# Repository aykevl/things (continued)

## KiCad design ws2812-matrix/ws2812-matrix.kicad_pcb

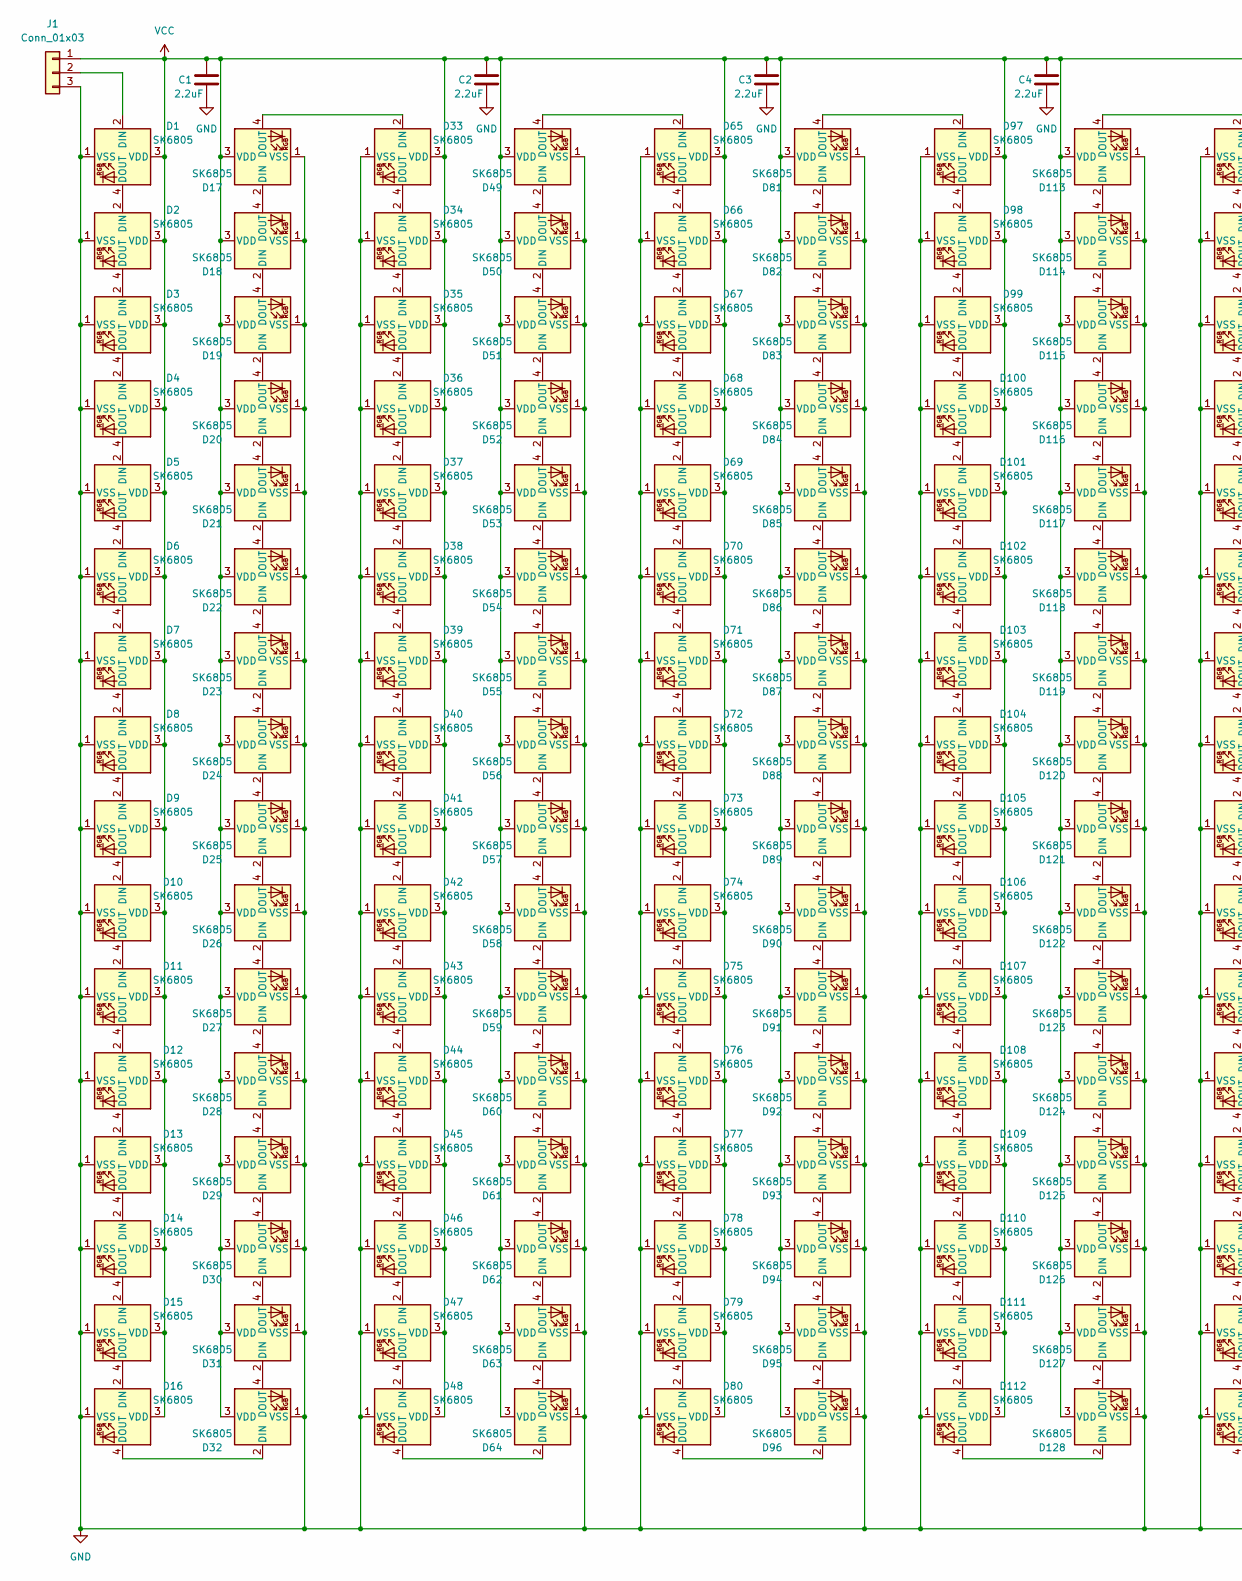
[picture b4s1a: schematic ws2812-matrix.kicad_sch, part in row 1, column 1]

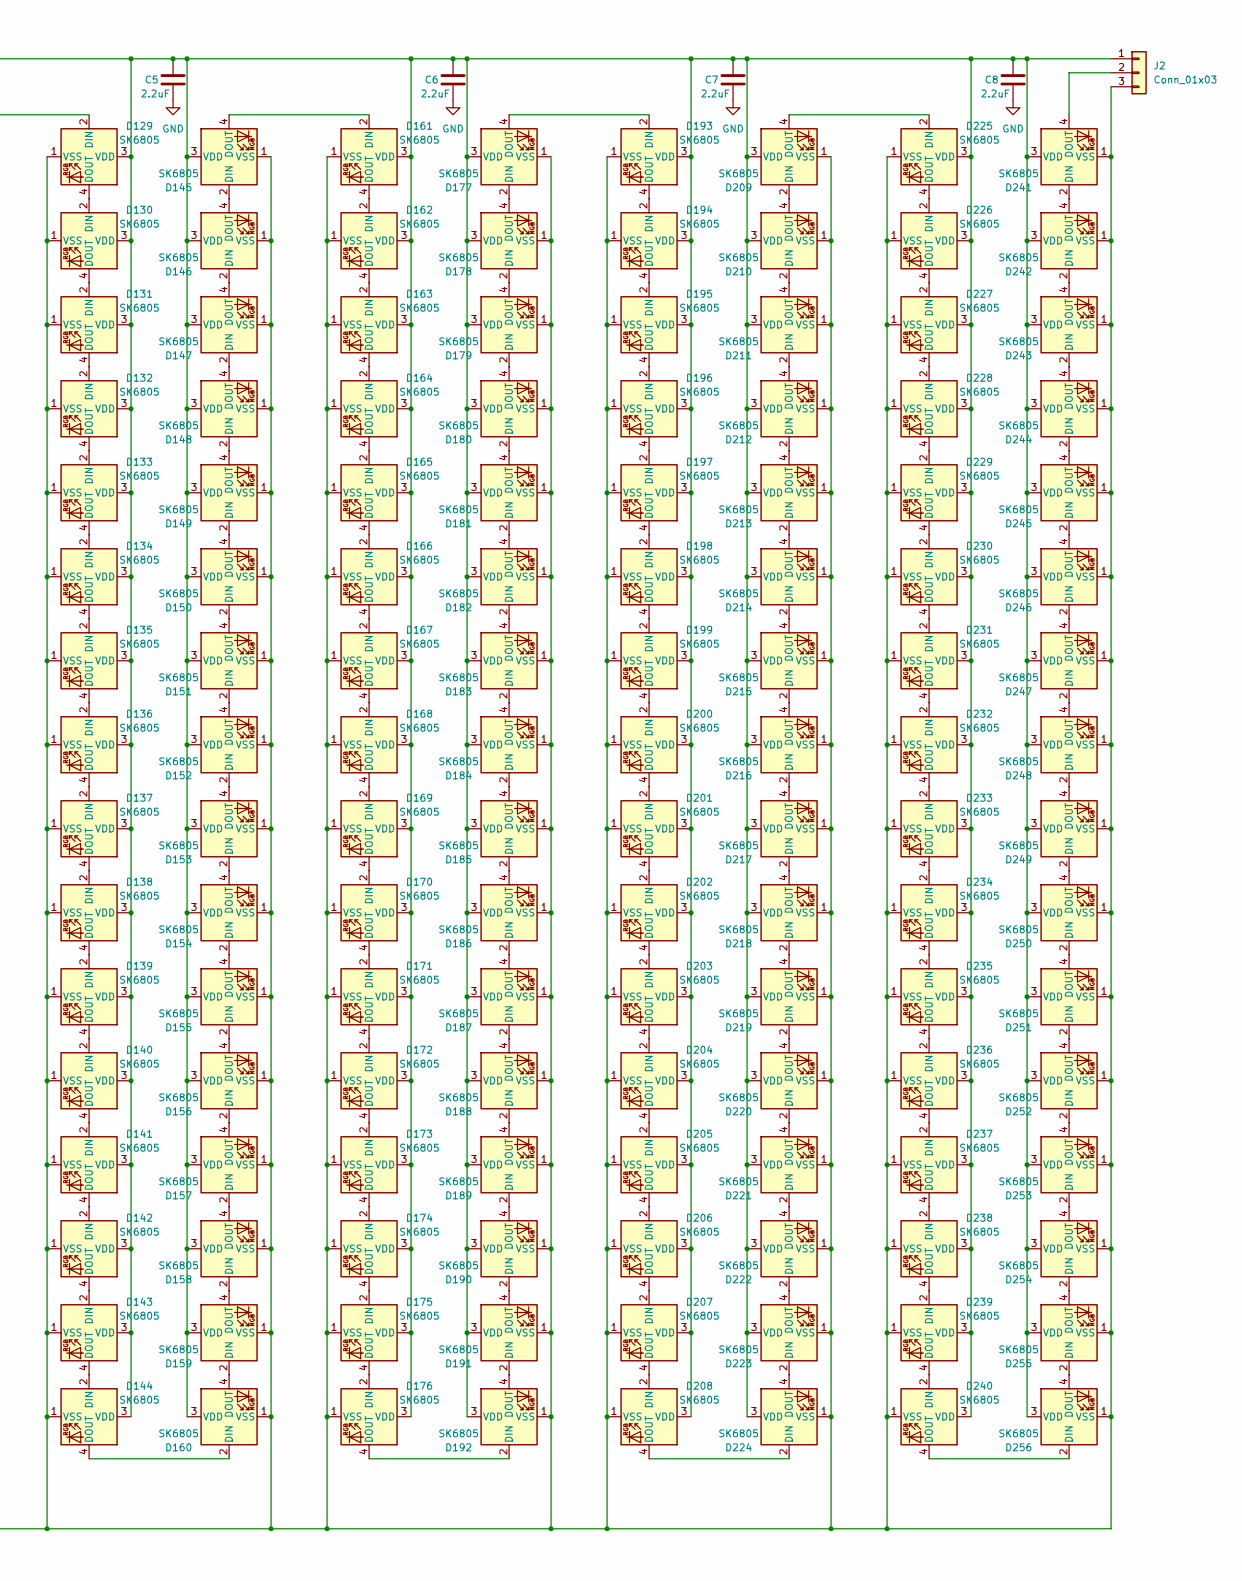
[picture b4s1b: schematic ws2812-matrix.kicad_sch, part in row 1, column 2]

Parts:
C1, C2, C3, C4, C5, C6, C7, C8: 2.2uF; C_0402_1005Metric; LCSC C12530
D1, D2, D3, D4, D5, D6, D7, D8, D9, D10, D11, D12, D13, D14, D15, D16, D17, D18, D19, D20, D21, D22, D23, D24, D25, D26, D27, D28, D29, D30, D31, D32, D33, D34, D35, D36, D37, D38, D39, D40, D41, D42, D43, D44, D45, D46, D47, D48, D49, D50, D51, D52, D53, D54, D55, D56, D57, D58, D59, D60, D61, D62, D63, D64, D65, D66, D67, D68, D69, D70, D71, D72, D73, D74, D75, D76, D77, D78, D79, D80, D81, D82, D83, D84, D85, D86, D87, D88, D89, D90, D91, D92, D93, D94, D95, D96, D97, D98, D99, D100, D101, D102, D103, D104, D105, D106, D107, D108, D109, D110, D111, D112, D113, D114, D115, D116, D117, D118, D119, D120, D121, D122, D123, D124, D125, D126, D127, D128, D129, D130, D131, D132, D133, D134, D135, D136, D137, D138, D139, D140, D141, D142, D143, D144, D145, D146, D147, D148, D149, D150, D151, D152, D153, D154, D155, D156, D157, D158, D159, D160, D161, D162, D163, D164, D165, D166, D167, D168, D169, D170, D171, D172, D173, D174, D175, D176, D177, D178, D179, D180, D181, D182, D183, D184, D185, D186, D187, D188, D189, D190, D191, D192, D193, D194, D195, D196, D197, D198, D199, D200, D201, D202, D203, D204, D205, D206, D207, D208, D209, D210, D211, D212, D213, D214, D215, D216, D217, D218, D219, D220, D221, D222, D223, D224, D225, D226, D227, D228, D229, D230, D231, D232, D233, D234, D235, D236, D237, D238, D239, D240, D241, D242, D243, D244, D245, D246, D247, D248, D249, D250, D251, D252, D253, D254, D255, D256: SK6805; SK6805-EC14; LCSC C2909055
J1, J2: Conn_01x03; WS2812-conn-oneside

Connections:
GND: C1.2, C2.2, C3.2, C4.2, C5.2, C6.2, C7.2, C8.2, D1.1 (VSS), D2.1 (VSS), D3.1 (VSS), D4.1 (VSS), D5.1 (VSS), D6.1 (VSS), D7.1 (VSS), D8.1 (VSS), D9.1 (VSS), D10.1 (VSS), D11.1 (VSS), D12.1 (VSS), D13.1 (VSS), D14.1 (VSS), D15.1 (VSS), D16.1 (VSS), D17.1 (VSS), D18.1 (VSS), D19.1 (VSS), D20.1 (VSS), D21.1 (VSS), D22.1 (VSS), D23.1 (VSS), D24.1 (VSS), D25.1 (VSS), D26.1 (VSS), D27.1 (VSS), D28.1 (VSS), D29.1 (VSS), D30.1 (VSS), D31.1 (VSS), D32.1 (VSS), D33.1 (VSS), D34.1 (VSS), D35.1 (VSS), D36.1 (VSS), D37.1 (VSS), D38.1 (VSS), D39.1 (VSS), D40.1 (VSS), D41.1 (VSS), D42.1 (VSS), D43.1 (VSS), D44.1 (VSS), D45.1 (VSS), D46.1 (VSS), D47.1 (VSS), D48.1 (VSS), D49.1 (VSS), D50.1 (VSS), D51.1 (VSS), D52.1 (VSS), D53.1 (VSS), D54.1 (VSS), D55.1 (VSS), D56.1 (VSS), D57.1 (VSS), D58.1 (VSS), D59.1 (VSS), D60.1 (VSS), D61.1 (VSS), D62.1 (VSS), D63.1 (VSS), D64.1 (VSS), D65.1 (VSS), D66.1 (VSS), D67.1 (VSS), D68.1 (VSS), D69.1 (VSS), D70.1 (VSS), D71.1 (VSS), D72.1 (VSS), D73.1 (VSS), D74.1 (VSS), D75.1 (VSS), D76.1 (VSS), D77.1 (VSS), D78.1 (VSS), D79.1 (VSS), D80.1 (VSS), D81.1 (VSS), D82.1 (VSS), D83.1 (VSS), D84.1 (VSS), D85.1 (VSS), D86.1 (VSS), D87.1 (VSS), D88.1 (VSS), D89.1 (VSS), D90.1 (VSS), D91.1 (VSS), D92.1 (VSS), D93.1 (VSS), D94.1 (VSS), D95.1 (VSS), D96.1 (VSS), D97.1 (VSS), D98.1 (VSS), D99.1 (VSS), D100.1 (VSS), D101.1 (VSS), D102.1 (VSS), D103.1 (VSS), D104.1 (VSS), D105.1 (VSS), D106.1 (VSS), D107.1 (VSS), D108.1 (VSS), D109.1 (VSS), D110.1 (VSS), D111.1 (VSS), D112.1 (VSS), D113.1 (VSS), D114.1 (VSS), D115.1 (VSS), D116.1 (VSS), D117.1 (VSS), D118.1 (VSS), D119.1 (VSS), D120.1 (VSS), D121.1 (VSS), D122.1 (VSS), D123.1 (VSS), D124.1 (VSS), D125.1 (VSS), D126.1 (VSS), D127.1 (VSS), D128.1 (VSS), D129.1 (VSS), D130.1 (VSS), D131.1 (VSS), D132.1 (VSS), D133.1 (VSS), D134.1 (VSS), D135.1 (VSS), D136.1 (VSS), D137.1 (VSS), D138.1 (VSS), D139.1 (VSS), D140.1 (VSS), D141.1 (VSS), D142.1 (VSS), D143.1 (VSS), D144.1 (VSS), D145.1 (VSS), D146.1 (VSS), D147.1 (VSS), D148.1 (VSS), D149.1 (VSS), D150.1 (VSS), D151.1 (VSS), D152.1 (VSS), D153.1 (VSS), D154.1 (VSS), D155.1 (VSS), D156.1 (VSS), D157.1 (VSS), D158.1 (VSS), D159.1 (VSS), D160.1 (VSS), D161.1 (VSS), D162.1 (VSS), D163.1 (VSS), D164.1 (VSS), D165.1 (VSS), D166.1 (VSS), D167.1 (VSS), D168.1 (VSS), D169.1 (VSS), D170.1 (VSS), D171.1 (VSS), D172.1 (VSS), D173.1 (VSS), D174.1 (VSS), D175.1 (VSS), D176.1 (VSS), D177.1 (VSS), D178.1 (VSS), D179.1 (VSS), D180.1 (VSS), D181.1 (VSS), D182.1 (VSS), D183.1 (VSS), D184.1 (VSS), D185.1 (VSS), D186.1 (VSS), D187.1 (VSS), D188.1 (VSS), D189.1 (VSS), D190.1 (VSS), D191.1 (VSS), D192.1 (VSS), D193.1 (VSS), D194.1 (VSS), D195.1 (VSS), D196.1 (VSS), D197.1 (VSS), D198.1 (VSS), D199.1 (VSS), D200.1 (VSS), D201.1 (VSS), D202.1 (VSS), D203.1 (VSS), D204.1 (VSS), D205.1 (VSS), D206.1 (VSS), D207.1 (VSS), D208.1 (VSS), D209.1 (VSS), D210.1 (VSS), D211.1 (VSS), D212.1 (VSS), D213.1 (VSS), D214.1 (VSS), D215.1 (VSS), D216.1 (VSS), D217.1 (VSS), D218.1 (VSS), D219.1 (VSS), D220.1 (VSS), D221.1 (VSS), D222.1 (VSS), D223.1 (VSS), D224.1 (VSS), D225.1 (VSS), D226.1 (VSS), D227.1 (VSS), D228.1 (VSS), D229.1 (VSS), D230.1 (VSS), D231.1 (VSS), D232.1 (VSS), D233.1 (VSS), D234.1 (VSS), D235.1 (VSS), D236.1 (VSS), D237.1 (VSS), D238.1 (VSS), D239.1 (VSS), D240.1 (VSS), D241.1 (VSS)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
unnamed: D1.2 (DIN), J1.2
unnamed: D1.4 (DOUT), D2.2 (DIN)
unnamed: D2.4 (DOUT), D3.2 (DIN)
unnamed: D3.4 (DOUT), D4.2 (DIN)
unnamed: D4.4 (DOUT), D5.2 (DIN)
unnamed: D5.4 (DOUT), D6.2 (DIN)
unnamed: D6.4 (DOUT), D7.2 (DIN)
unnamed: D7.4 (DOUT), D8.2 (DIN)
unnamed: D8.4 (DOUT), D9.2 (DIN)
unnamed: D9.4 (DOUT), D10.2 (DIN)
unnamed: D10.4 (DOUT), D11.2 (DIN)
unnamed: D11.4 (DOUT), D12.2 (DIN)
unnamed: D12.4 (DOUT), D13.2 (DIN)
unnamed: D13.4 (DOUT), D14.2 (DIN)
unnamed: D14.4 (DOUT), D15.2 (DIN)
unnamed: D15.4 (DOUT), D16.2 (DIN)
unnamed: D16.4 (DOUT), D32.2 (DIN)
unnamed: D17.2 (DIN), D18.4 (DOUT)
unnamed: D17.4 (DOUT), D33.2 (DIN)
unnamed: D18.2 (DIN), D19.4 (DOUT)
unnamed: D19.2 (DIN), D20.4 (DOUT)
unnamed: D20.2 (DIN), D21.4 (DOUT)
unnamed: D21.2 (DIN), D22.4 (DOUT)
unnamed: D22.2 (DIN), D23.4 (DOUT)
unnamed: D23.2 (DIN), D24.4 (DOUT)
unnamed: D24.2 (DIN), D25.4 (DOUT)
unnamed: D25.2 (DIN), D26.4 (DOUT)
unnamed: D26.2 (DIN), D27.4 (DOUT)
unnamed: D27.2 (DIN), D28.4 (DOUT)
unnamed: D28.2 (DIN), D29.4 (DOUT)
unnamed: D29.2 (DIN), D30.4 (DOUT)
unnamed: D30.2 (DIN), D31.4 (DOUT)
unnamed: D31.2 (DIN), D32.4 (DOUT)
unnamed: D33.4 (DOUT), D34.2 (DIN)
unnamed: D34.4 (DOUT), D35.2 (DIN)
unnamed: D35.4 (DOUT), D36.2 (DIN)
unnamed: D36.4 (DOUT), D37.2 (DIN)
unnamed: D37.4 (DOUT), D38.2 (DIN)
unnamed: D38.4 (DOUT), D39.2 (DIN)
unnamed: D39.4 (DOUT), D40.2 (DIN)
unnamed: D40.4 (DOUT), D41.2 (DIN)
unnamed: D41.4 (DOUT), D42.2 (DIN)
unnamed: D42.4 (DOUT), D43.2 (DIN)
unnamed: D43.4 (DOUT), D44.2 (DIN)
unnamed: D44.4 (DOUT), D45.2 (DIN)
unnamed: D45.4 (DOUT), D46.2 (DIN)
unnamed: D46.4 (DOUT), D47.2 (DIN)
unnamed: D47.4 (DOUT), D48.2 (DIN)
unnamed: D48.4 (DOUT), D64.2 (DIN)
unnamed: D49.2 (DIN), D50.4 (DOUT)
unnamed: D49.4 (DOUT), D65.2 (DIN)
unnamed: D50.2 (DIN), D51.4 (DOUT)
unnamed: D51.2 (DIN), D52.4 (DOUT)
unnamed: D52.2 (DIN), D53.4 (DOUT)
unnamed: D53.2 (DIN), D54.4 (DOUT)
unnamed: D54.2 (DIN), D55.4 (DOUT)
unnamed: D55.2 (DIN), D56.4 (DOUT)
unnamed: D56.2 (DIN), D57.4 (DOUT)
unnamed: D57.2 (DIN), D58.4 (DOUT)
unnamed: D58.2 (DIN), D59.4 (DOUT)
unnamed: D59.2 (DIN), D60.4 (DOUT)
unnamed: D60.2 (DIN), D61.4 (DOUT)
unnamed: D61.2 (DIN), D62.4 (DOUT)
unnamed: D62.2 (DIN), D63.4 (DOUT)
unnamed: D63.2 (DIN), D64.4 (DOUT)
unnamed: D65.4 (DOUT), D66.2 (DIN)
unnamed: D66.4 (DOUT), D67.2 (DIN)
unnamed: D67.4 (DOUT), D68.2 (DIN)
unnamed: D68.4 (DOUT), D69.2 (DIN)
unnamed: D69.4 (DOUT), D70.2 (DIN)
unnamed: D70.4 (DOUT), D71.2 (DIN)
unnamed: D71.4 (DOUT), D72.2 (DIN)
unnamed: D72.4 (DOUT), D73.2 (DIN)
unnamed: D73.4 (DOUT), D74.2 (DIN)
unnamed: D74.4 (DOUT), D75.2 (DIN)
unnamed: D75.4 (DOUT), D76.2 (DIN)
unnamed: D76.4 (DOUT), D77.2 (DIN)
unnamed: D77.4 (DOUT), D78.2 (DIN)
unnamed: D78.4 (DOUT), D79.2 (DIN)
unnamed: D79.4 (DOUT), D80.2 (DIN)
unnamed: D80.4 (DOUT), D96.2 (DIN)
unnamed: D81.2 (DIN), D82.4 (DOUT)
unnamed: D81.4 (DOUT), D97.2 (DIN)
unnamed: D82.2 (DIN), D83.4 (DOUT)
unnamed: D83.2 (DIN), D84.4 (DOUT)
unnamed: D84.2 (DIN), D85.4 (DOUT)
unnamed: D85.2 (DIN), D86.4 (DOUT)
unnamed: D86.2 (DIN), D87.4 (DOUT)
unnamed: D87.2 (DIN), D88.4 (DOUT)
unnamed: D88.2 (DIN), D89.4 (DOUT)
unnamed: D89.2 (DIN), D90.4 (DOUT)
unnamed: D90.2 (DIN), D91.4 (DOUT)
unnamed: D91.2 (DIN), D92.4 (DOUT)
unnamed: D92.2 (DIN), D93.4 (DOUT)
unnamed: D93.2 (DIN), D94.4 (DOUT)
unnamed: D94.2 (DIN), D95.4 (DOUT)
unnamed: D95.2 (DIN), D96.4 (DOUT)
unnamed: D97.4 (DOUT), D98.2 (DIN)
unnamed: D98.4 (DOUT), D99.2 (DIN)
unnamed: D99.4 (DOUT), D100.2 (DIN)
unnamed: D100.4 (DOUT), D101.2 (DIN)
unnamed: D101.4 (DOUT), D102.2 (DIN)
unnamed: D102.4 (DOUT), D103.2 (DIN)
unnamed: D103.4 (DOUT), D104.2 (DIN)
unnamed: D104.4 (DOUT), D105.2 (DIN)
unnamed: D105.4 (DOUT), D106.2 (DIN)
unnamed: D106.4 (DOUT), D107.2 (DIN)
unnamed: D107.4 (DOUT), D108.2 (DIN)
unnamed: D108.4 (DOUT), D109.2 (DIN)
unnamed: D109.4 (DOUT), D110.2 (DIN)
unnamed: D110.4 (DOUT), D111.2 (DIN)
unnamed: D111.4 (DOUT), D112.2 (DIN)
unnamed: D112.4 (DOUT), D128.2 (DIN)
unnamed: D113.2 (DIN), D114.4 (DOUT)
unnamed: D113.4 (DOUT), D129.2 (DIN)
unnamed: D114.2 (DIN), D115.4 (DOUT)
unnamed: D115.2 (DIN), D116.4 (DOUT)
unnamed: D116.2 (DIN), D117.4 (DOUT)
unnamed: D117.2 (DIN), D118.4 (DOUT)
unnamed: D118.2 (DIN), D119.4 (DOUT)
unnamed: D119.2 (DIN), D120.4 (DOUT)
unnamed: D120.2 (DIN), D121.4 (DOUT)
unnamed: D121.2 (DIN), D122.4 (DOUT)
unnamed: D122.2 (DIN), D123.4 (DOUT)
unnamed: D123.2 (DIN), D124.4 (DOUT)
unnamed: D124.2 (DIN), D125.4 (DOUT)
unnamed: D125.2 (DIN), D126.4 (DOUT)
unnamed: D126.2 (DIN), D127.4 (DOUT)
unnamed: D127.2 (DIN), D128.4 (DOUT)
unnamed: D129.4 (DOUT), D130.2 (DIN)
unnamed: D130.4 (DOUT), D131.2 (DIN)
unnamed: D131.4 (DOUT), D132.2 (DIN)
unnamed: D132.4 (DOUT), D133.2 (DIN)
unnamed: D133.4 (DOUT), D134.2 (DIN)
unnamed: D134.4 (DOUT), D135.2 (DIN)
unnamed: D135.4 (DOUT), D136.2 (DIN)
unnamed: D136.4 (DOUT), D137.2 (DIN)
unnamed: D137.4 (DOUT), D138.2 (DIN)
unnamed: D138.4 (DOUT), D139.2 (DIN)
unnamed: D139.4 (DOUT), D140.2 (DIN)
unnamed: D140.4 (DOUT), D141.2 (DIN)
unnamed: D141.4 (DOUT), D142.2 (DIN)
unnamed: D142.4 (DOUT), D143.2 (DIN)
unnamed: D143.4 (DOUT), D144.2 (DIN)
unnamed: D144.4 (DOUT), D160.2 (DIN)
unnamed: D145.2 (DIN), D146.4 (DOUT)
unnamed: D145.4 (DOUT), D161.2 (DIN)
unnamed: D146.2 (DIN), D147.4 (DOUT)
unnamed: D147.2 (DIN), D148.4 (DOUT)
unnamed: D148.2 (DIN), D149.4 (DOUT)
unnamed: D149.2 (DIN), D150.4 (DOUT)
unnamed: D150.2 (DIN), D151.4 (DOUT)
unnamed: D151.2 (DIN), D152.4 (DOUT)
unnamed: D152.2 (DIN), D153.4 (DOUT)
unnamed: D153.2 (DIN), D154.4 (DOUT)
unnamed: D154.2 (DIN), D155.4 (DOUT)
unnamed: D155.2 (DIN), D156.4 (DOUT)
unnamed: D156.2 (DIN), D157.4 (DOUT)
unnamed: D157.2 (DIN), D158.4 (DOUT)
unnamed: D158.2 (DIN), D159.4 (DOUT)
unnamed: D159.2 (DIN), D160.4 (DOUT)
unnamed: D161.4 (DOUT), D162.2 (DIN)
unnamed: D162.4 (DOUT), D163.2 (DIN)
unnamed: D163.4 (DOUT), D164.2 (DIN)
unnamed: D164.4 (DOUT), D165.2 (DIN)
unnamed: D165.4 (DOUT), D166.2 (DIN)
unnamed: D166.4 (DOUT), D167.2 (DIN)
unnamed: D167.4 (DOUT), D168.2 (DIN)
unnamed: D168.4 (DOUT), D169.2 (DIN)
unnamed: D169.4 (DOUT), D170.2 (DIN)
unnamed: D170.4 (DOUT), D171.2 (DIN)
unnamed: D171.4 (DOUT), D172.2 (DIN)
unnamed: D172.4 (DOUT), D173.2 (DIN)
unnamed: D173.4 (DOUT), D174.2 (DIN)
unnamed: D174.4 (DOUT), D175.2 (DIN)
unnamed: D175.4 (DOUT), D176.2 (DIN)
unnamed: D176.4 (DOUT), D192.2 (DIN)
unnamed: D177.2 (DIN), D178.4 (DOUT)
unnamed: D177.4 (DOUT), D193.2 (DIN)
unnamed: D178.2 (DIN), D179.4 (DOUT)
unnamed: D179.2 (DIN), D180.4 (DOUT)
unnamed: D180.2 (DIN), D181.4 (DOUT)
unnamed: D181.2 (DIN), D182.4 (DOUT)
unnamed: D182.2 (DIN), D183.4 (DOUT)
unnamed: D183.2 (DIN), D184.4 (DOUT)
unnamed: D184.2 (DIN), D185.4 (DOUT)
unnamed: D185.2 (DIN), D186.4 (DOUT)
unnamed: D186.2 (DIN), D187.4 (DOUT)
unnamed: D187.2 (DIN), D188.4 (DOUT)
unnamed: D188.2 (DIN), D189.4 (DOUT)
unnamed: D189.2 (DIN), D190.4 (DOUT)
unnamed: D190.2 (DIN), D191.4 (DOUT)
unnamed: D191.2 (DIN), D192.4 (DOUT)
unnamed: D193.4 (DOUT), D194.2 (DIN)
unnamed: D194.4 (DOUT), D195.2 (DIN)
unnamed: D195.4 (DOUT), D196.2 (DIN)
unnamed: D196.4 (DOUT), D197.2 (DIN)
unnamed: D197.4 (DOUT), D198.2 (DIN)
unnamed: D198.4 (DOUT), D199.2 (DIN)
unnamed: D199.4 (DOUT), D200.2 (DIN)
unnamed: D200.4 (DOUT), D201.2 (DIN)
unnamed: D201.4 (DOUT), D202.2 (DIN)
unnamed: D202.4 (DOUT), D203.2 (DIN)
unnamed: D203.4 (DOUT), D204.2 (DIN)
unnamed: D204.4 (DOUT), D205.2 (DIN)
unnamed: D205.4 (DOUT), D206.2 (DIN)
unnamed: D206.4 (DOUT), D207.2 (DIN)
unnamed: D207.4 (DOUT), D208.2 (DIN)
unnamed: D208.4 (DOUT), D224.2 (DIN)
unnamed: D209.2 (DIN), D210.4 (DOUT)
unnamed: D209.4 (DOUT), D225.2 (DIN)
unnamed: D210.2 (DIN), D211.4 (DOUT)
unnamed: D211.2 (DIN), D212.4 (DOUT)
unnamed: D212.2 (DIN), D213.4 (DOUT)
unnamed: D213.2 (DIN), D214.4 (DOUT)
unnamed: D214.2 (DIN), D215.4 (DOUT)
unnamed: D215.2 (DIN), D216.4 (DOUT)
unnamed: D216.2 (DIN), D217.4 (DOUT)
unnamed: D217.2 (DIN), D218.4 (DOUT)
unnamed: D218.2 (DIN), D219.4 (DOUT)
unnamed: D219.2 (DIN), D220.4 (DOUT)
unnamed: D220.2 (DIN), D221.4 (DOUT)
unnamed: D221.2 (DIN), D222.4 (DOUT)
unnamed: D222.2 (DIN), D223.4 (DOUT)
unnamed: D223.2 (DIN), D224.4 (DOUT)
unnamed: D225.4 (DOUT), D226.2 (DIN)
unnamed: D226.4 (DOUT), D227.2 (DIN)
unnamed: D227.4 (DOUT), D228.2 (DIN)
unnamed: D228.4 (DOUT), D229.2 (DIN)
unnamed: D229.4 (DOUT), D230.2 (DIN)
unnamed: D230.4 (DOUT), D231.2 (DIN)
unnamed: D231.4 (DOUT), D232.2 (DIN)
unnamed: D232.4 (DOUT), D233.2 (DIN)
unnamed: D233.4 (DOUT), D234.2 (DIN)
unnamed: D234.4 (DOUT), D235.2 (DIN)
unnamed: D235.4 (DOUT), D236.2 (DIN)
unnamed: D236.4 (DOUT), D237.2 (DIN)
unnamed: D237.4 (DOUT), D238.2 (DIN)
unnamed: D238.4 (DOUT), D239.2 (DIN)
unnamed: D239.4 (DOUT), D240.2 (DIN)
unnamed: D240.4 (DOUT), D256.2 (DIN)
unnamed: D241.2 (DIN), D242.4 (DOUT)
unnamed: D241.4 (DOUT), J2.2
unnamed: D242.2 (DIN), D243.4 (DOUT)
unnamed: D243.2 (DIN), D244.4 (DOUT)
unnamed: D244.2 (DIN), D245.4 (DOUT)
unnamed: D245.2 (DIN), D246.4 (DOUT)
unnamed: D246.2 (DIN), D247.4 (DOUT)
unnamed: D247.2 (DIN), D248.4 (DOUT)
unnamed: D248.2 (DIN), D249.4 (DOUT)
unnamed: D249.2 (DIN), D250.4 (DOUT)
unnamed: D250.2 (DIN), D251.4 (DOUT)
unnamed: D251.2 (DIN), D252.4 (DOUT)
unnamed: D252.2 (DIN), D253.4 (DOUT)
unnamed: D253.2 (DIN), D254.4 (DOUT)
unnamed: D254.2 (DIN), D255.4 (DOUT)
unnamed: D255.2 (DIN), D256.4 (DOUT)
VCC: C1.1, C2.1, C3.1, C4.1, C5.1, C6.1, C7.1, C8.1, D1.3 (VDD), D2.3 (VDD), D3.3 (VDD), D4.3 (VDD), D5.3 (VDD), D6.3 (VDD), D7.3 (VDD), D8.3 (VDD), D9.3 (VDD), D10.3 (VDD), D11.3 (VDD), D12.3 (VDD), D13.3 (VDD), D14.3 (VDD), D15.3 (VDD), D16.3 (VDD), D17.3 (VDD), D18.3 (VDD), D19.3 (VDD), D20.3 (VDD), D21.3 (VDD), D22.3 (VDD), D23.3 (VDD), D24.3 (VDD), D25.3 (VDD), D26.3 (VDD), D27.3 (VDD), D28.3 (VDD), D29.3 (VDD), D30.3 (VDD), D31.3 (VDD), D32.3 (VDD), D33.3 (VDD), D34.3 (VDD), D35.3 (VDD), D36.3 (VDD), D37.3 (VDD), D38.3 (VDD), D39.3 (VDD), D40.3 (VDD), D41.3 (VDD), D42.3 (VDD), D43.3 (VDD), D44.3 (VDD), D45.3 (VDD), D46.3 (VDD), D47.3 (VDD), D48.3 (VDD), D49.3 (VDD), D50.3 (VDD), D51.3 (VDD), D52.3 (VDD), D53.3 (VDD), D54.3 (VDD), D55.3 (VDD), D56.3 (VDD), D57.3 (VDD), D58.3 (VDD), D59.3 (VDD), D60.3 (VDD), D61.3 (VDD), D62.3 (VDD), D63.3 (VDD), D64.3 (VDD), D65.3 (VDD), D66.3 (VDD), D67.3 (VDD), D68.3 (VDD), D69.3 (VDD), D70.3 (VDD), D71.3 (VDD), D72.3 (VDD), D73.3 (VDD), D74.3 (VDD), D75.3 (VDD), D76.3 (VDD), D77.3 (VDD), D78.3 (VDD), D79.3 (VDD), D80.3 (VDD), D81.3 (VDD), D82.3 (VDD), D83.3 (VDD), D84.3 (VDD), D85.3 (VDD), D86.3 (VDD), D87.3 (VDD), D88.3 (VDD), D89.3 (VDD), D90.3 (VDD), D91.3 (VDD), D92.3 (VDD), D93.3 (VDD), D94.3 (VDD), D95.3 (VDD), D96.3 (VDD), D97.3 (VDD), D98.3 (VDD), D99.3 (VDD), D100.3 (VDD), D101.3 (VDD), D102.3 (VDD), D103.3 (VDD), D104.3 (VDD), D105.3 (VDD), D106.3 (VDD), D107.3 (VDD), D108.3 (VDD), D109.3 (VDD), D110.3 (VDD), D111.3 (VDD), D112.3 (VDD), D113.3 (VDD), D114.3 (VDD), D115.3 (VDD), D116.3 (VDD), D117.3 (VDD), D118.3 (VDD), D119.3 (VDD), D120.3 (VDD), D121.3 (VDD), D122.3 (VDD), D123.3 (VDD), D124.3 (VDD), D125.3 (VDD), D126.3 (VDD), D127.3 (VDD), D128.3 (VDD), D129.3 (VDD), D130.3 (VDD), D131.3 (VDD), D132.3 (VDD), D133.3 (VDD), D134.3 (VDD), D135.3 (VDD), D136.3 (VDD), D137.3 (VDD), D138.3 (VDD), D139.3 (VDD), D140.3 (VDD), D141.3 (VDD), D142.3 (VDD), D143.3 (VDD), D144.3 (VDD), D145.3 (VDD), D146.3 (VDD), D147.3 (VDD), D148.3 (VDD), D149.3 (VDD), D150.3 (VDD), D151.3 (VDD), D152.3 (VDD), D153.3 (VDD), D154.3 (VDD), D155.3 (VDD), D156.3 (VDD), D157.3 (VDD), D158.3 (VDD), D159.3 (VDD), D160.3 (VDD), D161.3 (VDD), D162.3 (VDD), D163.3 (VDD), D164.3 (VDD), D165.3 (VDD), D166.3 (VDD), D167.3 (VDD), D168.3 (VDD), D169.3 (VDD), D170.3 (VDD), D171.3 (VDD), D172.3 (VDD), D173.3 (VDD), D174.3 (VDD), D175.3 (VDD), D176.3 (VDD), D177.3 (VDD), D178.3 (VDD), D179.3 (VDD), D180.3 (VDD), D181.3 (VDD), D182.3 (VDD), D183.3 (VDD), D184.3 (VDD), D185.3 (VDD), D186.3 (VDD), D187.3 (VDD), D188.3 (VDD), D189.3 (VDD), D190.3 (VDD), D191.3 (VDD), D192.3 (VDD), D193.3 (VDD), D194.3 (VDD), D195.3 (VDD), D196.3 (VDD), D197.3 (VDD), D198.3 (VDD), D199.3 (VDD), D200.3 (VDD), D201.3 (VDD), D202.3 (VDD), D203.3 (VDD), D204.3 (VDD), D205.3 (VDD), D206.3 (VDD), D207.3 (VDD), D208.3 (VDD), D209.3 (VDD), D210.3 (VDD), D211.3 (VDD), D212.3 (VDD), D213.3 (VDD), D214.3 (VDD), D215.3 (VDD), D216.3 (VDD), D217.3 (VDD), D218.3 (VDD), D219.3 (VDD), D220.3 (VDD), D221.3 (VDD), D222.3 (VDD), D223.3 (VDD), D224.3 (VDD), D225.3 (VDD), D226.3 (VDD), D227.3 (VDD), D228.3 (VDD), D229.3 (VDD), D230.3 (VDD), D231.3 (VDD), D232.3 (VDD), D233.3 (VDD), D234.3 (VDD), D235.3 (VDD), D236.3 (VDD), D237.3 (VDD), D238.3 (VDD), D239.3 (VDD), D240.3 (VDD), D241.3 (VDD)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

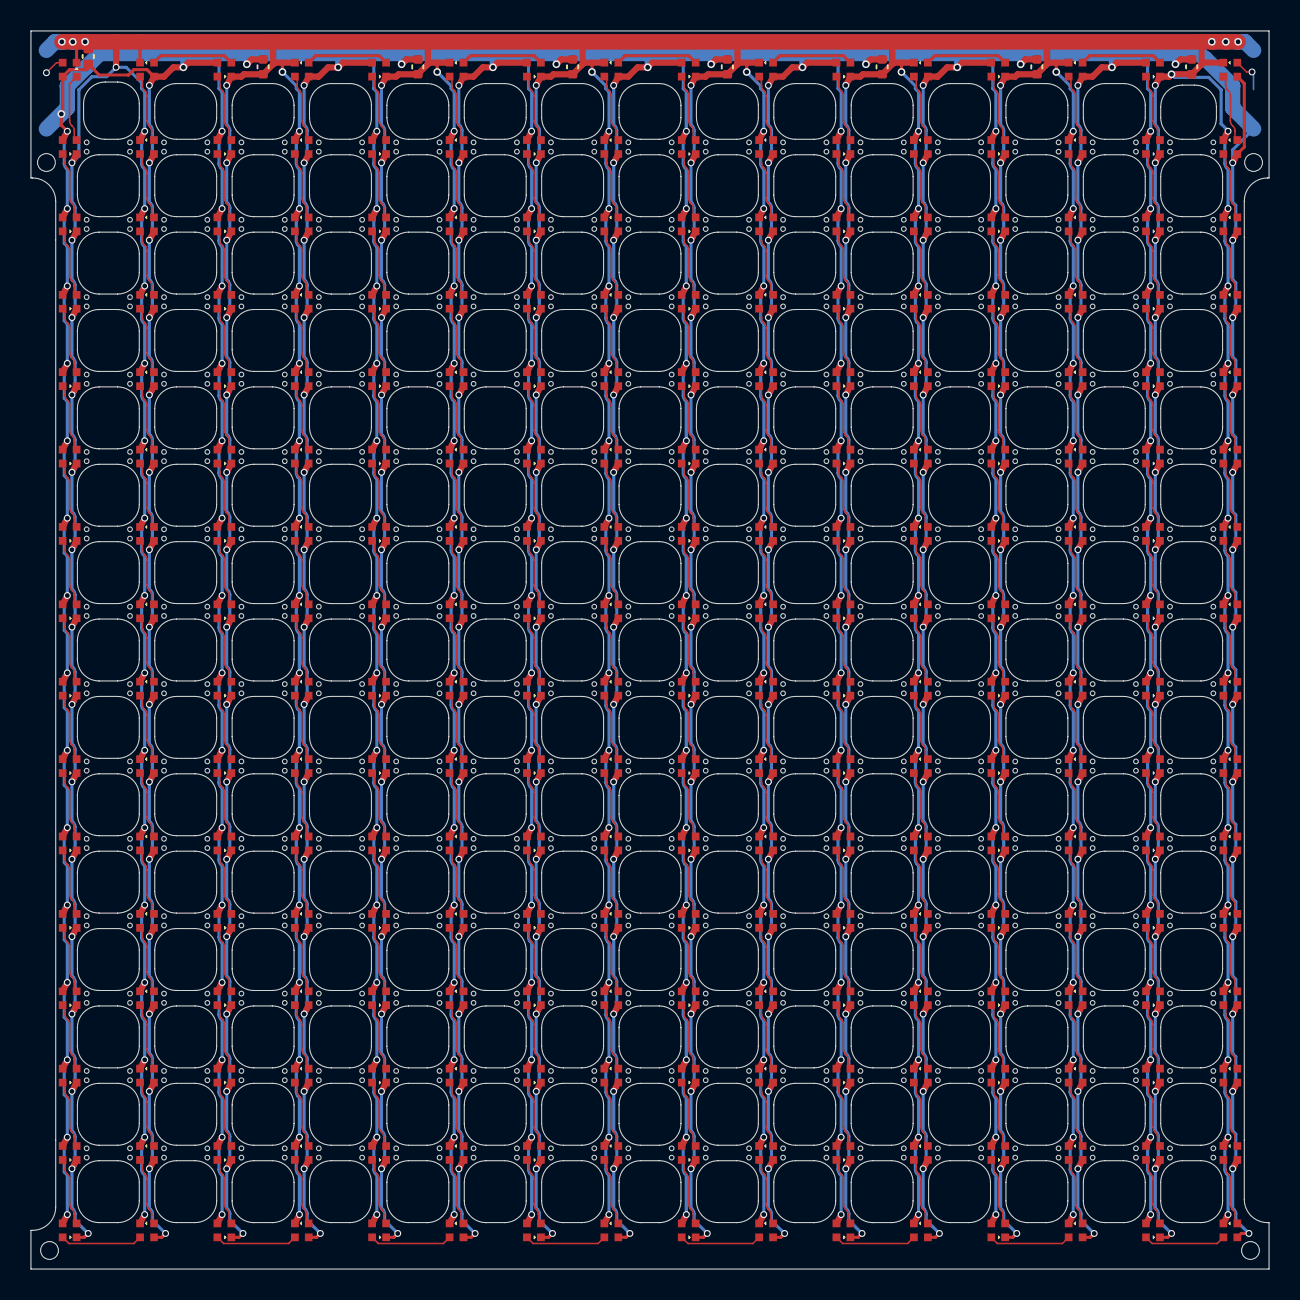
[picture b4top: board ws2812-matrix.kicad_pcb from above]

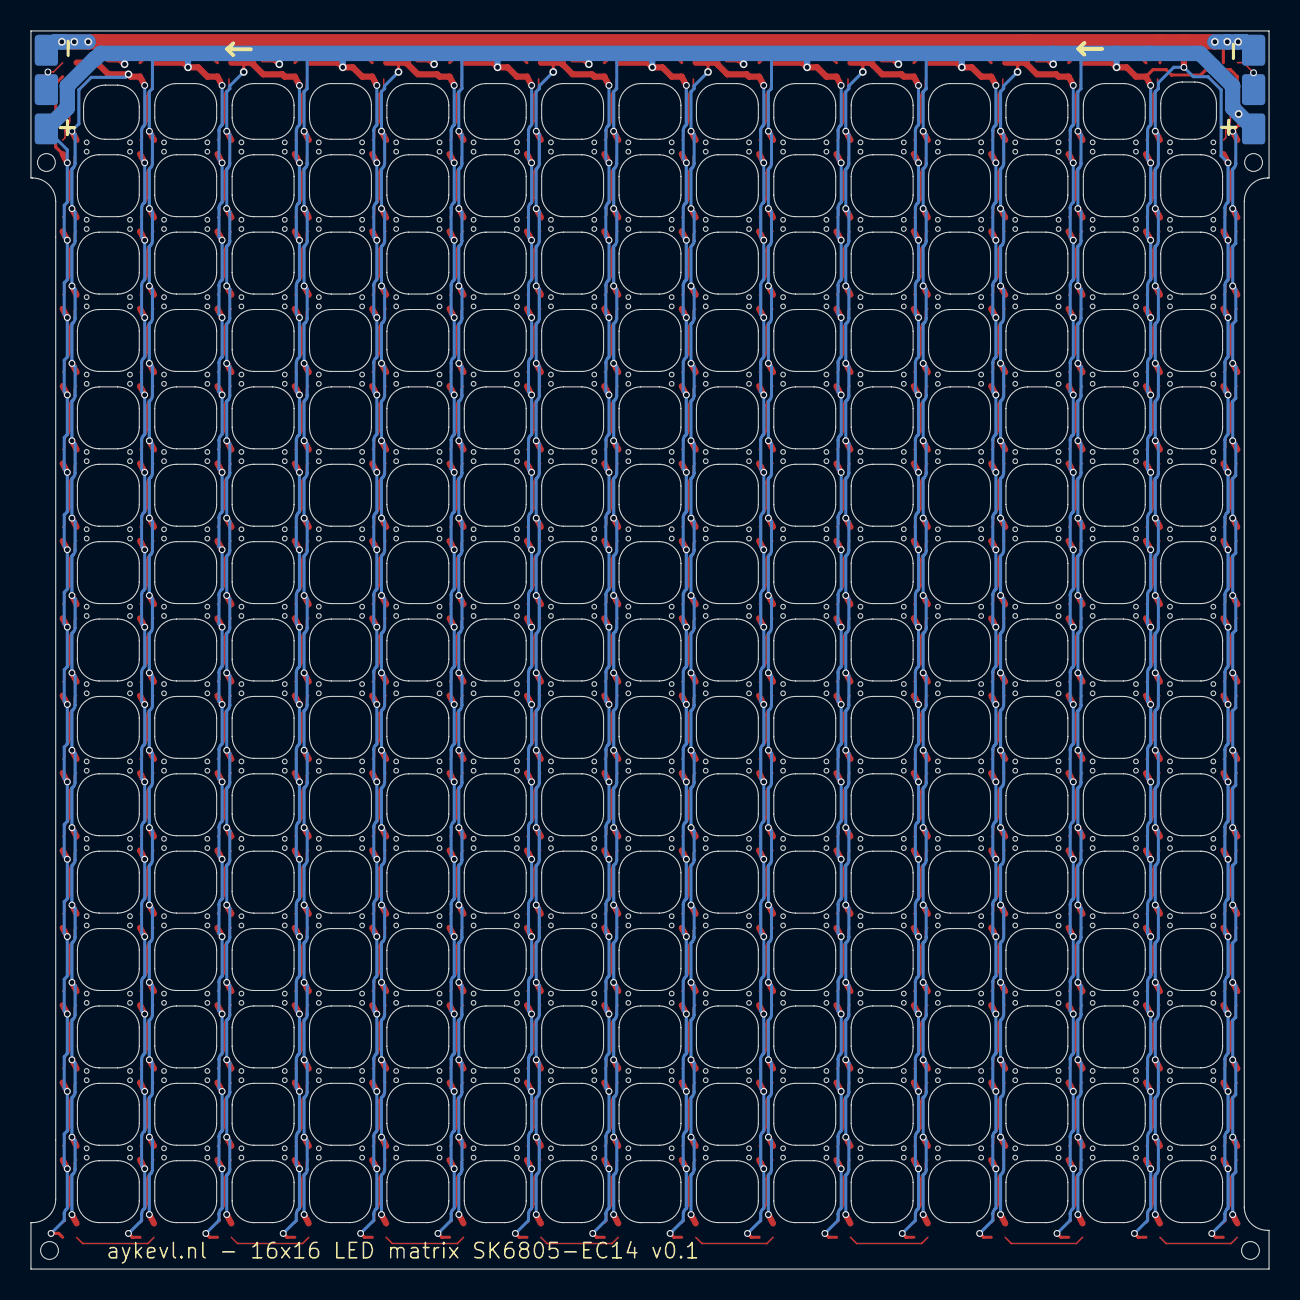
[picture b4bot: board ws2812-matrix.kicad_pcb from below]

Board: 2 copper layers, 80.0 x 80.0 mm, 266 parts (2 on the bottom side), 259 nets.

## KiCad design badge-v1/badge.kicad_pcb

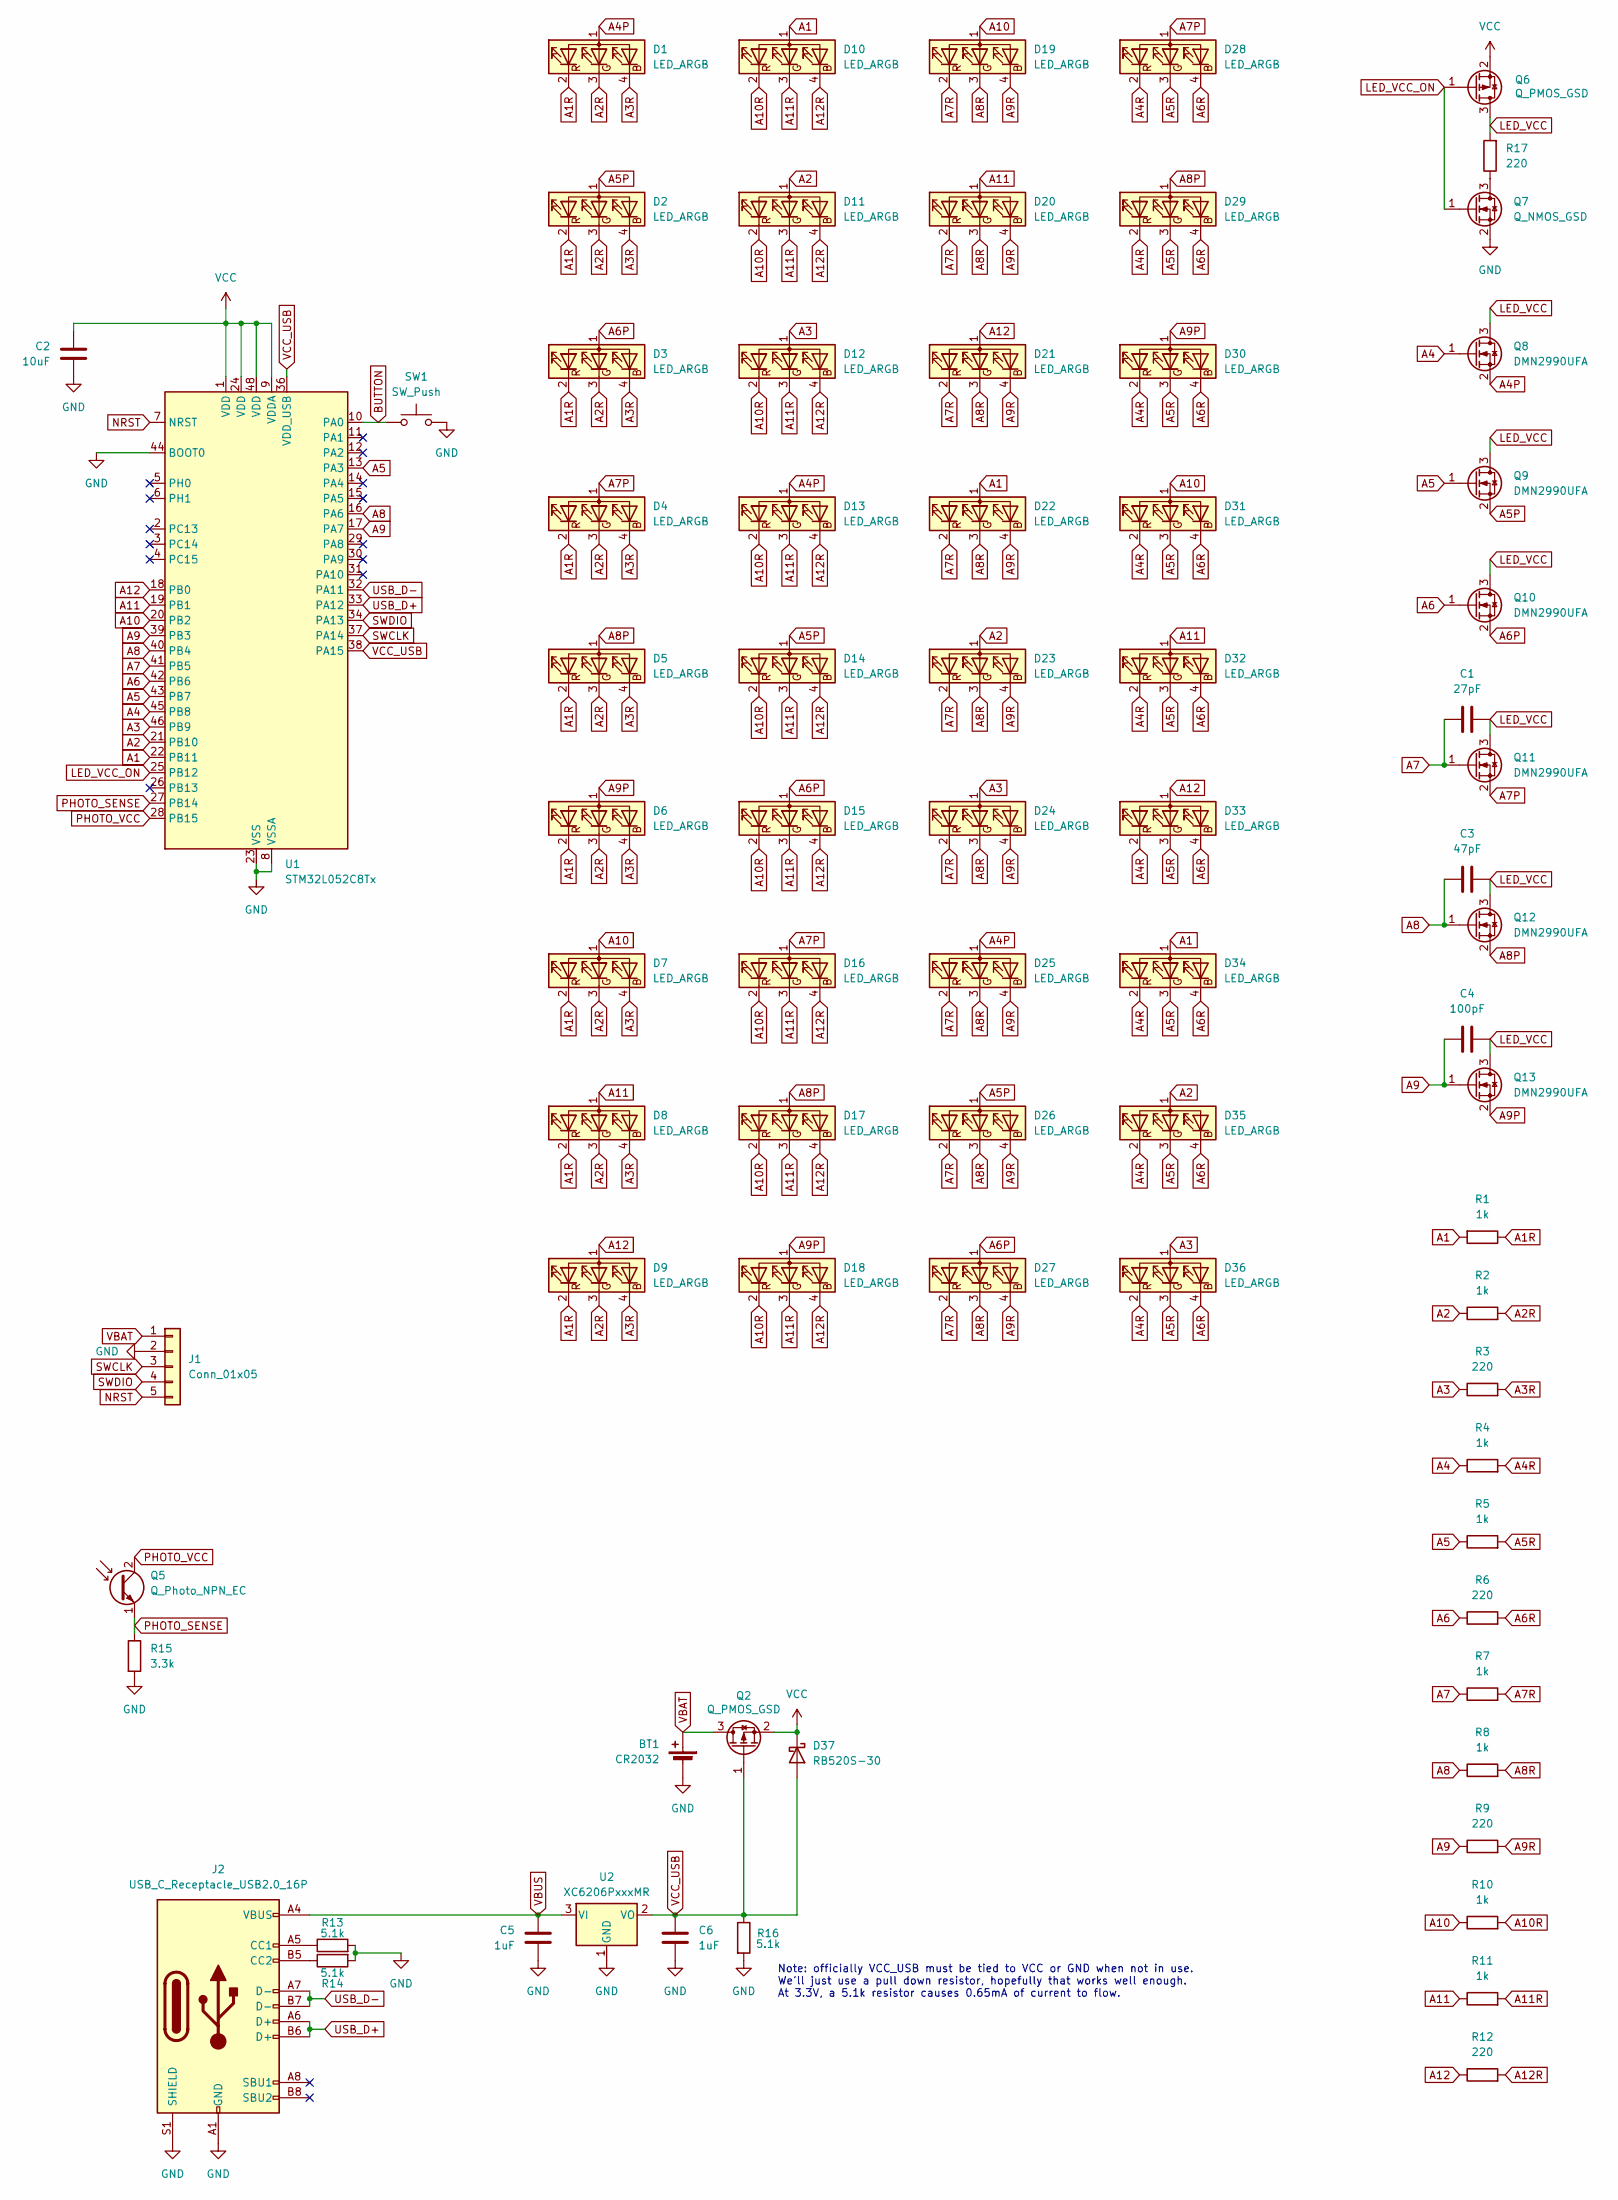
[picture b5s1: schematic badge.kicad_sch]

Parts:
BT1: CR2032; BatteryHolder_Keystone_1060_1x2032; LCSC C70377
C1: 27pF; C_0402_1005Metric; LCSC C1557
C2: 10uF; C_0402_1005Metric; LCSC C15525
C3: 47pF; C_0402_1005Metric; LCSC C1567
C4: 100pF; C_0402_1005Metric; LCSC C1546
C5, C6: 1uF; C_0402_1005Metric; LCSC C52923
D1, D2, D3, D4, D5, D6, D7, D8, D9, D10, D11, D12, D13, D14, D15, D16, D17, D18, D19, D20, D21, D22, D23, D24, D25, D26, D27, D28, D29, D30, D31, D32, D33, D34, D35, D36: LED_ARGB; NH-Z1415RGBA-SG; LCSC C2874117
D37: RB520S-30; D_SOD-523; LCSC C7502701
J1: Conn_01x05; ProgramHeader
J2: USB_C_Receptacle_USB2.0_16P; USB_C_Receptacle_G-Switch_GT-USB-7010ASV; LCSC C393939
Q2, Q6: Q_PMOS_GSD; SOT-23; LCSC C427391
Q5: Q_Photo_NPN_EC; PT19-21C_L41_TR8; LCSC C20416370
Q7: Q_NMOS_GSD; SOT-23; LCSC C28646272
Q8, Q9, Q10, Q11, Q12, Q13: DMN2990UFA; LCSC C151598
R1, R2, R4, R5, R7, R8, R10, R11: 1k; R_0402_1005Metric; LCSC C11702
R3, R6, R9, R12, R17: 220; R_0402_1005Metric; LCSC C25091
R13, R14, R16: 5.1k; R_0402_1005Metric; LCSC C25905
R15: 3.3k; R_0402_1005Metric; LCSC C25890
SW1: SW_Push; SW_Push_SPST_NO_Alps_SKRK; LCSC C720477
U1: STM32L052C8Tx; LQFP-48_7x7mm_P0.5mm; LCSC C111213
U2: XC6206PxxxMR; SOT-23-3; LCSC C5446

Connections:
A1: D10.1 (A), D22.1 (A), D34.1 (A), R1.2, U1.22 (PB11)
A1R: D1.2 (RK), D2.2 (RK), D3.2 (RK), D4.2 (RK), D5.2 (RK), D6.2 (RK), D7.2 (RK), D8.2 (RK), D9.2 (RK), R1.1
A2: D11.1 (A), D23.1 (A), D35.1 (A), R2.1, U1.21 (PB10)
A2R: D1.3 (GK), D2.3 (GK), D3.3 (GK), D4.3 (GK), D5.3 (GK), D6.3 (GK), D7.3 (GK), D8.3 (GK), D9.3 (GK), R2.2
A3: D12.1 (A), D24.1 (A), D36.1 (A), R3.1, U1.46 (PB9)
A3R: D1.4 (BK), D2.4 (BK), D3.4 (BK), D4.4 (BK), D5.4 (BK), D6.4 (BK), D7.4 (BK), D8.4 (BK), D9.4 (BK), R3.2
A4: Q8.1 (G), R4.1, U1.45 (PB8)
A4P: D1.1 (A), D13.1 (A), D25.1 (A), Q8.2 (S)
A4R: D28.2 (RK), D29.2 (RK), D30.2 (RK), D31.2 (RK), D32.2 (RK), D33.2 (RK), D34.2 (RK), D35.2 (RK), D36.2 (RK), R4.2
A5: Q9.1 (G), R5.1, U1.13 (PA3), U1.43 (PB7)
A5P: D2.1 (A), D14.1 (A), D26.1 (A), Q9.2 (S)
A5R: D28.3 (GK), D29.3 (GK), D30.3 (GK), D31.3 (GK), D32.3 (GK), D33.3 (GK), D34.3 (GK), D35.3 (GK), D36.3 (GK), R5.2
A6: Q10.1 (G), R6.1, U1.42 (PB6)
A6P: D3.1 (A), D15.1 (A), D27.1 (A), Q10.2 (S)
A6R: D28.4 (BK), D29.4 (BK), D30.4 (BK), D31.4 (BK), D32.4 (BK), D33.4 (BK), D34.4 (BK), D35.4 (BK), D36.4 (BK), R6.2
A7: C1.1, Q11.1 (G), R7.1, U1.41 (PB5)
A7P: D4.1 (A), D16.1 (A), D28.1 (A), Q11.2 (S)
A7R: D19.2 (RK), D20.2 (RK), D21.2 (RK), D22.2 (RK), D23.2 (RK), D24.2 (RK), D25.2 (RK), D26.2 (RK), D27.2 (RK), R7.2
A8: C3.1, Q12.1 (G), R8.1, U1.16 (PA6), U1.40 (PB4)
A8P: D5.1 (A), D17.1 (A), D29.1 (A), Q12.2 (S)
A8R: D19.3 (GK), D20.3 (GK), D21.3 (GK), D22.3 (GK), D23.3 (GK), D24.3 (GK), D25.3 (GK), D26.3 (GK), D27.3 (GK), R8.2
A9: C4.1, Q13.1 (G), R9.1, U1.17 (PA7), U1.39 (PB3)
A9P: D6.1 (A), D18.1 (A), D30.1 (A), Q13.2 (S)
A9R: D19.4 (BK), D20.4 (BK), D21.4 (BK), D22.4 (BK), D23.4 (BK), D24.4 (BK), D25.4 (BK), D26.4 (BK), D27.4 (BK), R9.2
A10: D7.1 (A), D19.1 (A), D31.1 (A), R10.1, U1.20 (PB2)
A10R: D10.2 (RK), D11.2 (RK), D12.2 (RK), D13.2 (RK), D14.2 (RK), D15.2 (RK), D16.2 (RK), D17.2 (RK), D18.2 (RK), R10.2
A11: D8.1 (A), D20.1 (A), D32.1 (A), R11.1, U1.19 (PB1)
A11R: D10.3 (GK), D11.3 (GK), D12.3 (GK), D13.3 (GK), D14.3 (GK), D15.3 (GK), D16.3 (GK), D17.3 (GK), D18.3 (GK), R11.2
A12: D9.1 (A), D21.1 (A), D33.1 (A), R12.1, U1.18 (PB0)
A12R: D10.4 (BK), D11.4 (BK), D12.4 (BK), D13.4 (BK), D14.4 (BK), D15.4 (BK), D16.4 (BK), D17.4 (BK), D18.4 (BK), R12.2
BUTTON: SW1.2, U1.10 (PA0)
GND: BT1.2 (-), C2.2, C5.2, C6.2, J1.2, J2.A1 (GND), J2.A12 (GND), J2.B1 (GND), J2.B12 (GND), J2.S1 (SHIELD), Q7.2 (S), R13.2, R14.2, R15.2, R16.2, SW1.1, U1.8 (VSSA), U1.23 (VSS), U1.35 (VSS), U1.44 (BOOT0), U1.47 (VSS), U2.1 (GND)
LED_VCC: C1.2, C3.2, C4.2, Q6.3 (D), Q8.3 (D), Q9.3 (D), Q10.3 (D), Q11.3 (D), Q12.3 (D), Q13.3 (D), R17.2
LED_VCC_ON: Q6.1 (G), Q7.1 (G), U1.25 (PB12)
NRST: J1.5, U1.7 (NRST)
unnamed: J2.A5 (CC1), R13.1
unnamed: J2.B5 (CC2), R14.1
unnamed: Q7.3 (D), R17.1
PHOTO_SENSE: Q5.1 (E), R15.1, U1.27 (PB14)
PHOTO_VCC: Q5.2 (C), U1.28 (PB15)
SWCLK: J1.3, U1.37 (PA14)
SWDIO: J1.4, U1.34 (PA13)
USB_D+: J2.A6 (D+), J2.B6 (D+), U1.33 (PA12)
USB_D-: J2.A7 (D-), J2.B7 (D-), U1.32 (PA11)
VBAT: BT1.1 (+), J1.1, Q2.3 (D)
VBUS: C5.1, J2.A4 (VBUS), J2.A9 (VBUS), J2.B4 (VBUS), J2.B9 (VBUS), U2.3 (VI)
VCC: C2.1, D37.1 (K), Q2.2 (S), Q6.2 (S), U1.1 (VDD), U1.9 (VDDA), U1.24 (VDD), U1.48 (VDD)
VCC_USB: C6.1, D37.2 (A), Q2.1 (G), R16.1, U1.36 (VDD_USB), U1.38 (PA15), U2.2 (VO)

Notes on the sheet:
Note: officially VCC_USB must be tied to VCC or GND when not in use. We'll just use a pull down resistor, hopefully that works well enough. At 3.3V, a 5.1k resistor causes 0.65mA of current to flow.

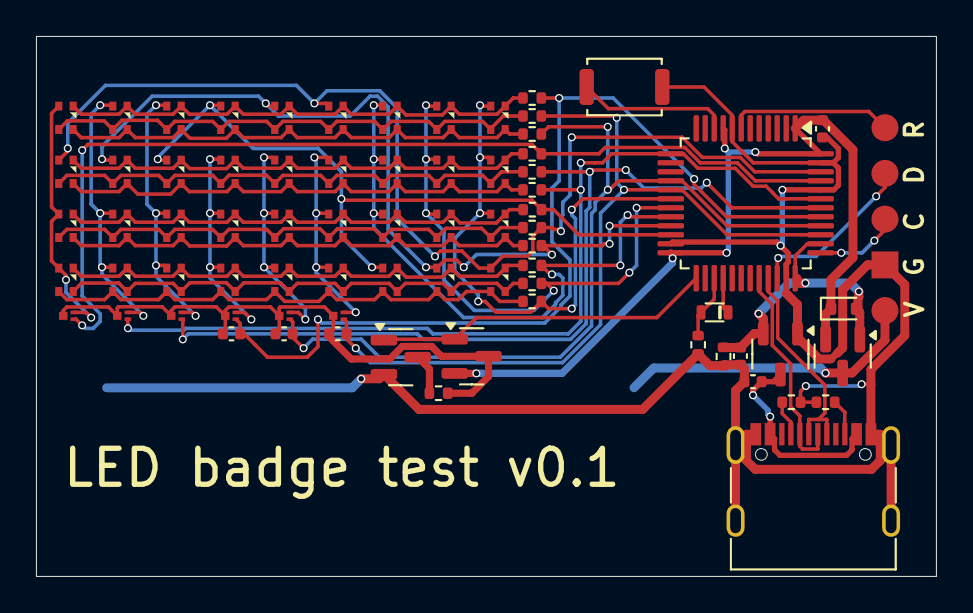
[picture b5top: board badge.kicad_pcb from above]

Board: 2 copper layers, 50.0 x 30.0 mm, 76 parts (1 on the bottom side), 48 nets.
